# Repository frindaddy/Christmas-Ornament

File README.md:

# Christmas Ornament

A battery-powered, shake-activated LED ornament built around a Puya PY32F002B microcontroller. The KiCad files contain the schematic and PCB design; the firmware sleeps until the vibration switch detects movement, then alternates two LED groups.

## How It Works

- A CR2032 coin cell powers the board.
- An HX-0805-C2 vibration switch signals movement to PB0.
- The MCU wakes from STOP mode on either edge of the switch signal.
- Two LED groups, driven through N-channel MOSFETs from PB1 and PA7, alternate every 250 ms for about 5 seconds.
- The MCU returns to STOP mode after the pattern finishes.

The firmware targets the PY32F002BL15S7TU in an SOP-8 package. Battery life depends on the assembled circuit, components, and usage; no measured runtime is specified here.

## Repository Layout

| Path | Contents |
| --- | --- |
| [`hardware/Ornament.kicad_sch`](hardware/Ornament.kicad_sch) | KiCad schematic |
| [`hardware/Ornament.kicad_pcb`](hardware/Ornament.kicad_pcb) | KiCad PCB layout |
| [`hardware/Ornament.pretty/`](hardware/Ornament.pretty/) | Project-specific KiCad footprints |
| [`datasheets/`](datasheets/) | PY32F002B datasheet and reference manual |
| [`software/main.c`](software/main.c) | Application firmware |
| [`software/ornament.uvprojx`](software/ornament.uvprojx) | Keil µVision project |
| [`software/PY32F0xx_Drivers/`](software/PY32F0xx_Drivers/) | Used Puya low-level GPIO and EXTI driver sources |

## Firmware Pin Map

| MCU pin | Function |
| --- | --- |
| PB0 | Vibration switch input; external pull resistor is provided by the board |
| PB1 | LED group A MOSFET gate |
| PA7 | LED group B MOSFET gate |
| PA2 | SWCLK programming/debug signal |
| PB6 | SWDIO programming/debug signal |

## Build and Flash

The firmware project is configured for Keil µVision, Arm Compiler 6.24, and the Puya `PY32F0xx_DFP` device pack (version 1.2.8 in the project settings).

1. Install Keil MDK/µVision and the Puya PY32F0xx device family pack.
2. Open [`software/ornament.uvprojx`](software/ornament.uvprojx) in µVision and select the `Target_1` target.
3. Build the project. The configured executable output is `software/Objects/ornament.axf`.
4. Connect a SWD programmer to SWCLK (PA2), SWDIO (PB6), and the board's power/ground, then use µVision's download/debug controls to program the MCU.

## Hardware

Open the schematic and PCB in KiCad. The project includes custom footprints under `hardware/Ornament.pretty/` and local symbol/footprint table configuration files in `hardware/`. Confirm the selected fabrication settings and the PCB revision before ordering boards.

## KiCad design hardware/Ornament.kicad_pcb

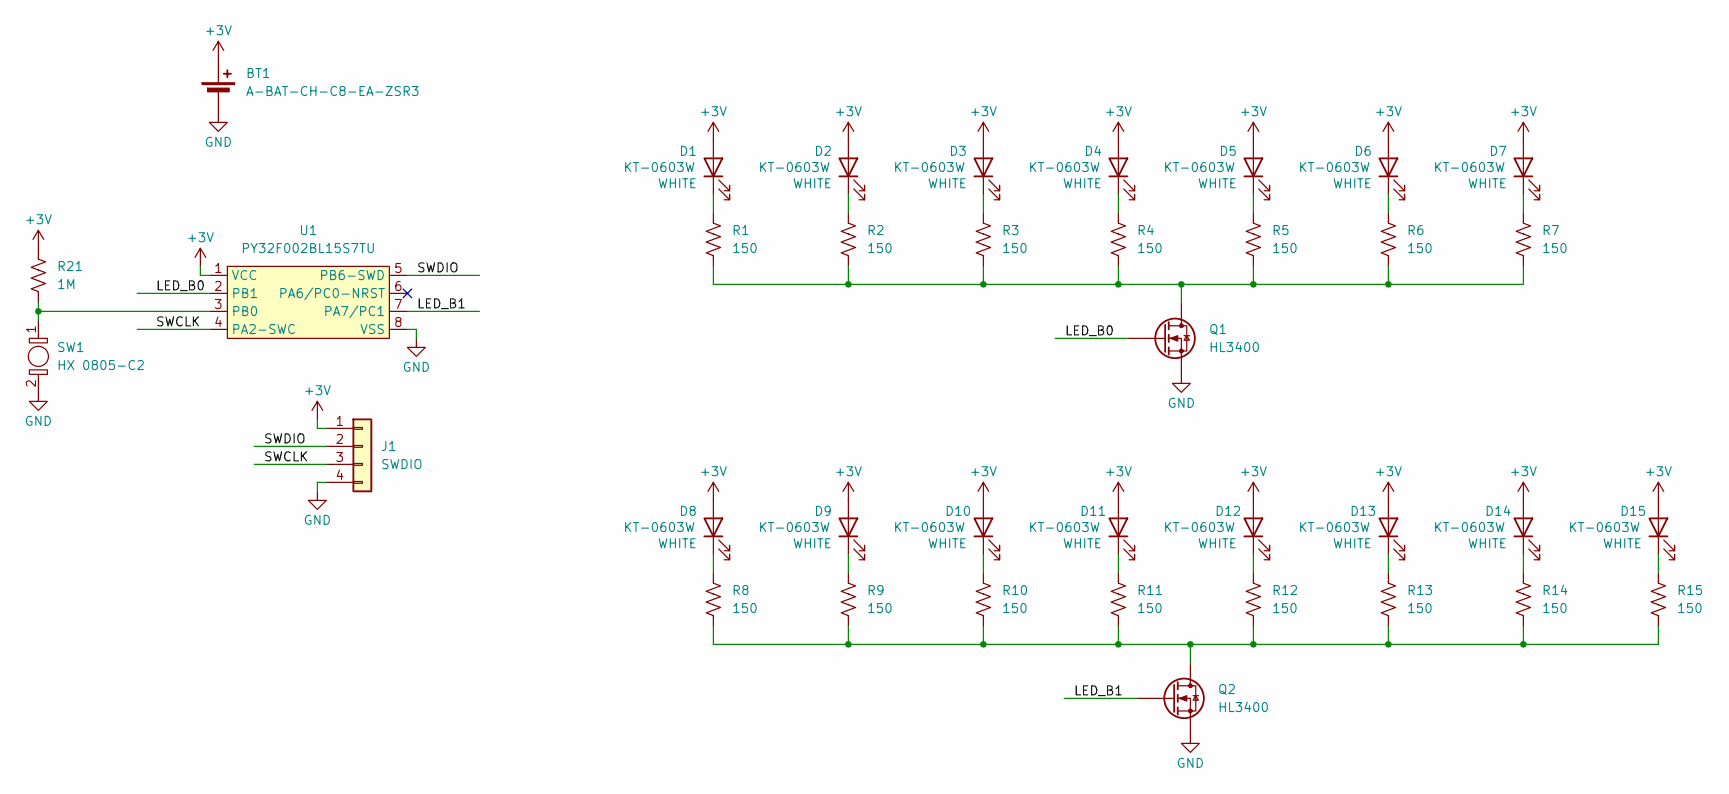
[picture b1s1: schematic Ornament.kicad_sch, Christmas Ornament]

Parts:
BT1: A-BAT-CH-C8-EA-ZSR3; CR2032-BS-6-1
D1, D2, D3, D4, D5, D6, D7, D8, D9, D10, D11, D12, D13, D14, D15: KT-0603W; LED_0603_1608Metric_Pad1.05x0.95mm_HandSolder; JLCPCB Part Number KT-0603W
J1: SWDIO; SWD_SMT_Pads
Q1, Q2: HL3400; SOT-23; JLCPCB Part Number C22469448
R1, R2, R3, R4, R5, R6, R7, R8, R9, R10, R11, R12, R13, R14, R15: 150; R_0603_1608Metric_Pad0.98x0.95mm_HandSolder; JLCPCB Part Number C22808
R21: 1M; R_0603_1608Metric_Pad0.98x0.95mm_HandSolder; JLCPCB Part Number C22935
SW1: HX 0805-C2; R_0805_2012Metric; JLCPCB Part Number C42371121
U1: PY32F002BL15S7TU; SOP-8_3.76x4.96mm_P1.27mm; JLCPCB Part Number C49424671

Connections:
+3V: BT1.1 (+), D1.2 (A), D2.2 (A), D3.2 (A), D4.2 (A), D5.2 (A), D6.2 (A), D7.2 (A), D8.2 (A), D9.2 (A), D10.2 (A), D11.2 (A), D12.2 (A), D13.2 (A), D14.2 (A), D15.2 (A), J1.1, R21.1, U1.1 (VCC)
/LED_B0: Q1.1 (G), U1.2 (PB1)
/LED_B1: Q2.1 (G), U1.7 (PA7/PC1)
/SWCLK: J1.3, U1.4 (PA2-SWC)
/SWDIO: J1.2, U1.5 (PB6-SWD)
GND: BT1.2 (-), J1.4, Q1.2 (S), Q2.2 (S), SW1.2, U1.8 (VSS)
unnamed: D1.1 (K), R1.1
unnamed: D2.1 (K), R2.1
unnamed: D3.1 (K), R3.1
unnamed: D4.1 (K), R4.1
unnamed: D5.1 (K), R5.1
unnamed: D6.1 (K), R6.1
unnamed: D7.1 (K), R7.1
unnamed: D8.1 (K), R8.1
unnamed: D9.1 (K), R9.1
unnamed: D10.1 (K), R10.1
unnamed: D11.1 (K), R11.1
unnamed: D12.1 (K), R12.1
unnamed: D13.1 (K), R13.1
unnamed: D14.1 (K), R14.1
unnamed: D15.1 (K), R15.1
unnamed: Q1.3 (D), R1.2, R2.2, R3.2, R4.2, R5.2, R6.2, R7.2
unnamed: Q2.3 (D), R8.2, R9.2, R10.2, R11.2, R12.2, R13.2, R14.2, R15.2
unnamed: R21.2, SW1.1, U1.3 (PB0)

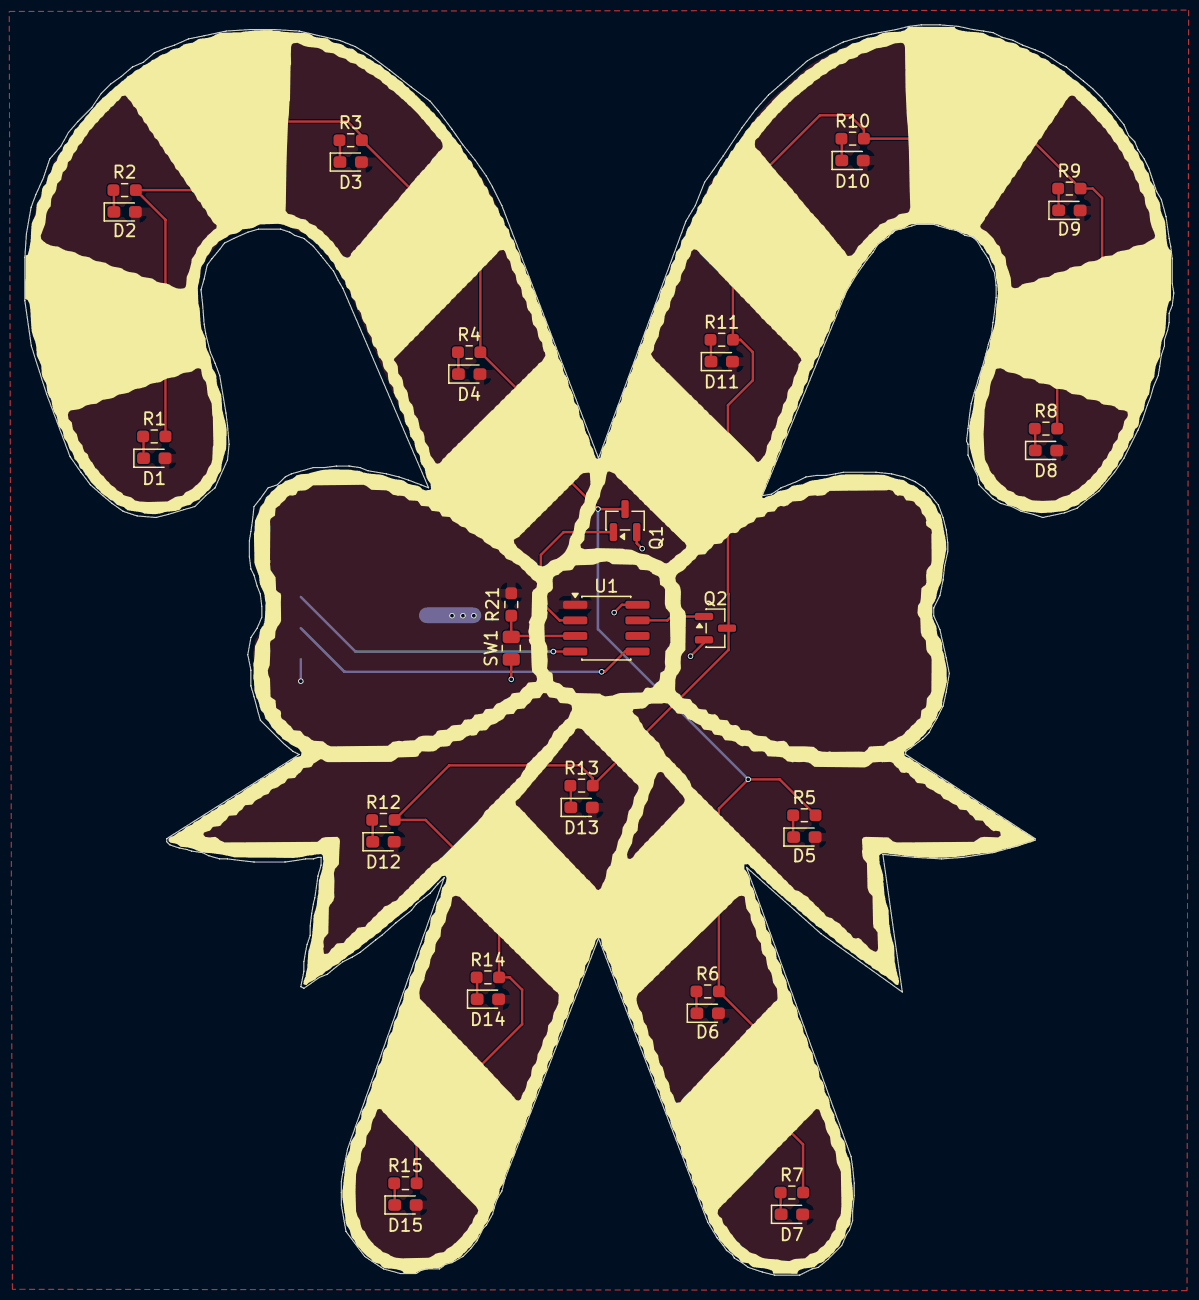
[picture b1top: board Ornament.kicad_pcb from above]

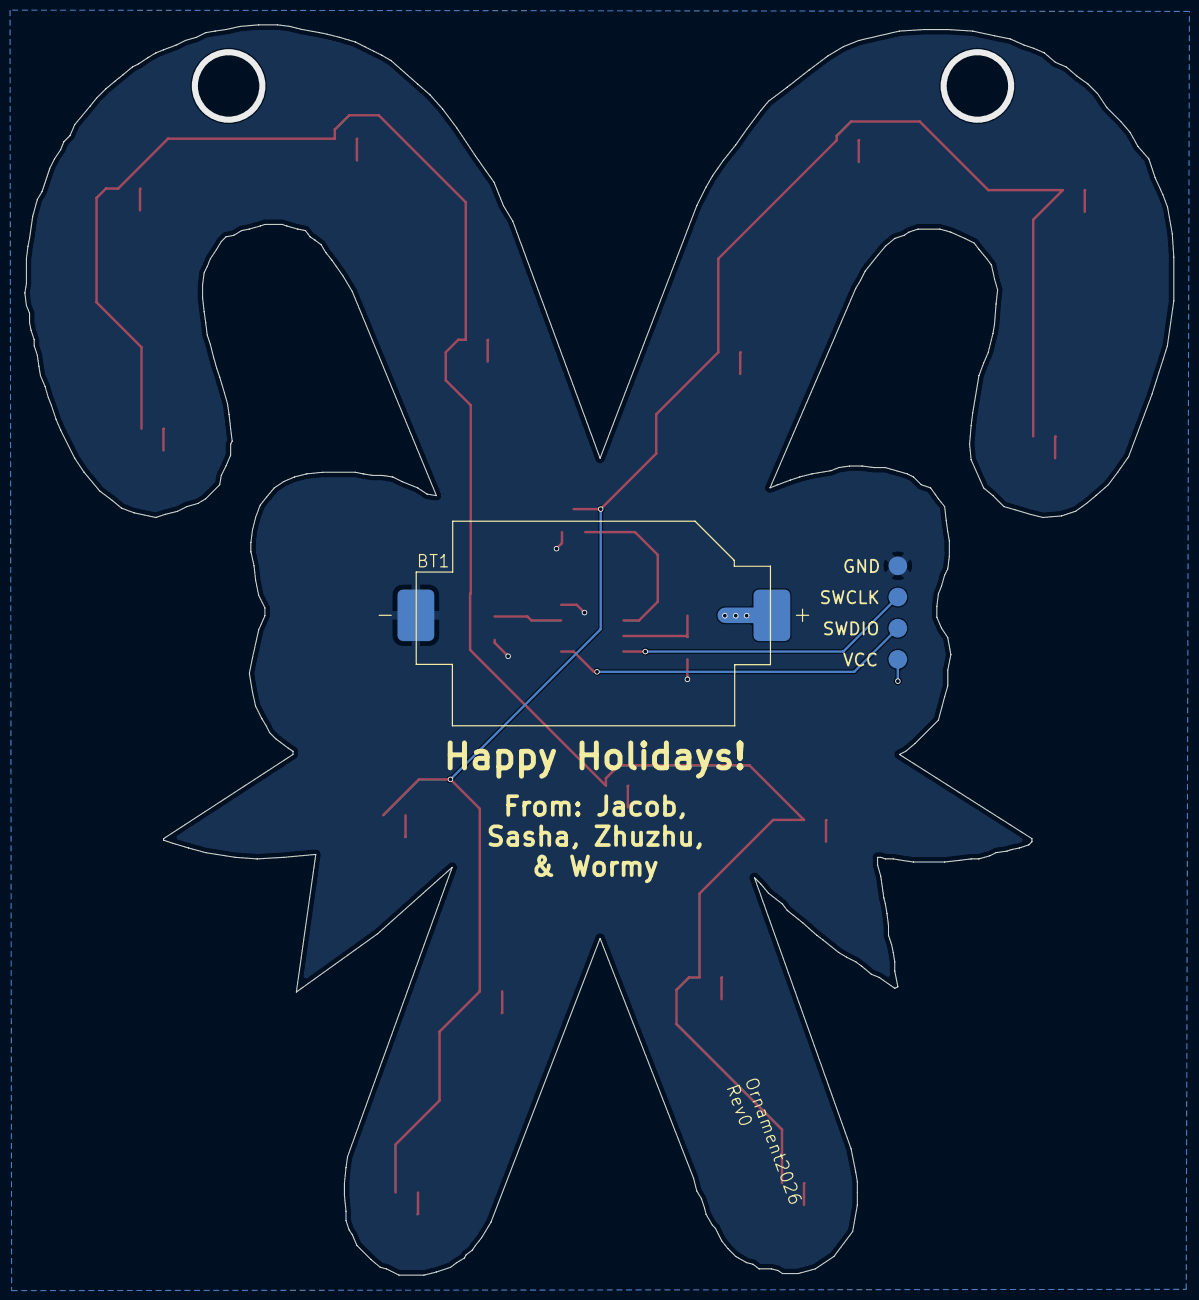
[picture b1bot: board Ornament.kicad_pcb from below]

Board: 2 copper layers, 93.6 x 101.9 mm, 37 parts (2 on the bottom side), 24 nets.

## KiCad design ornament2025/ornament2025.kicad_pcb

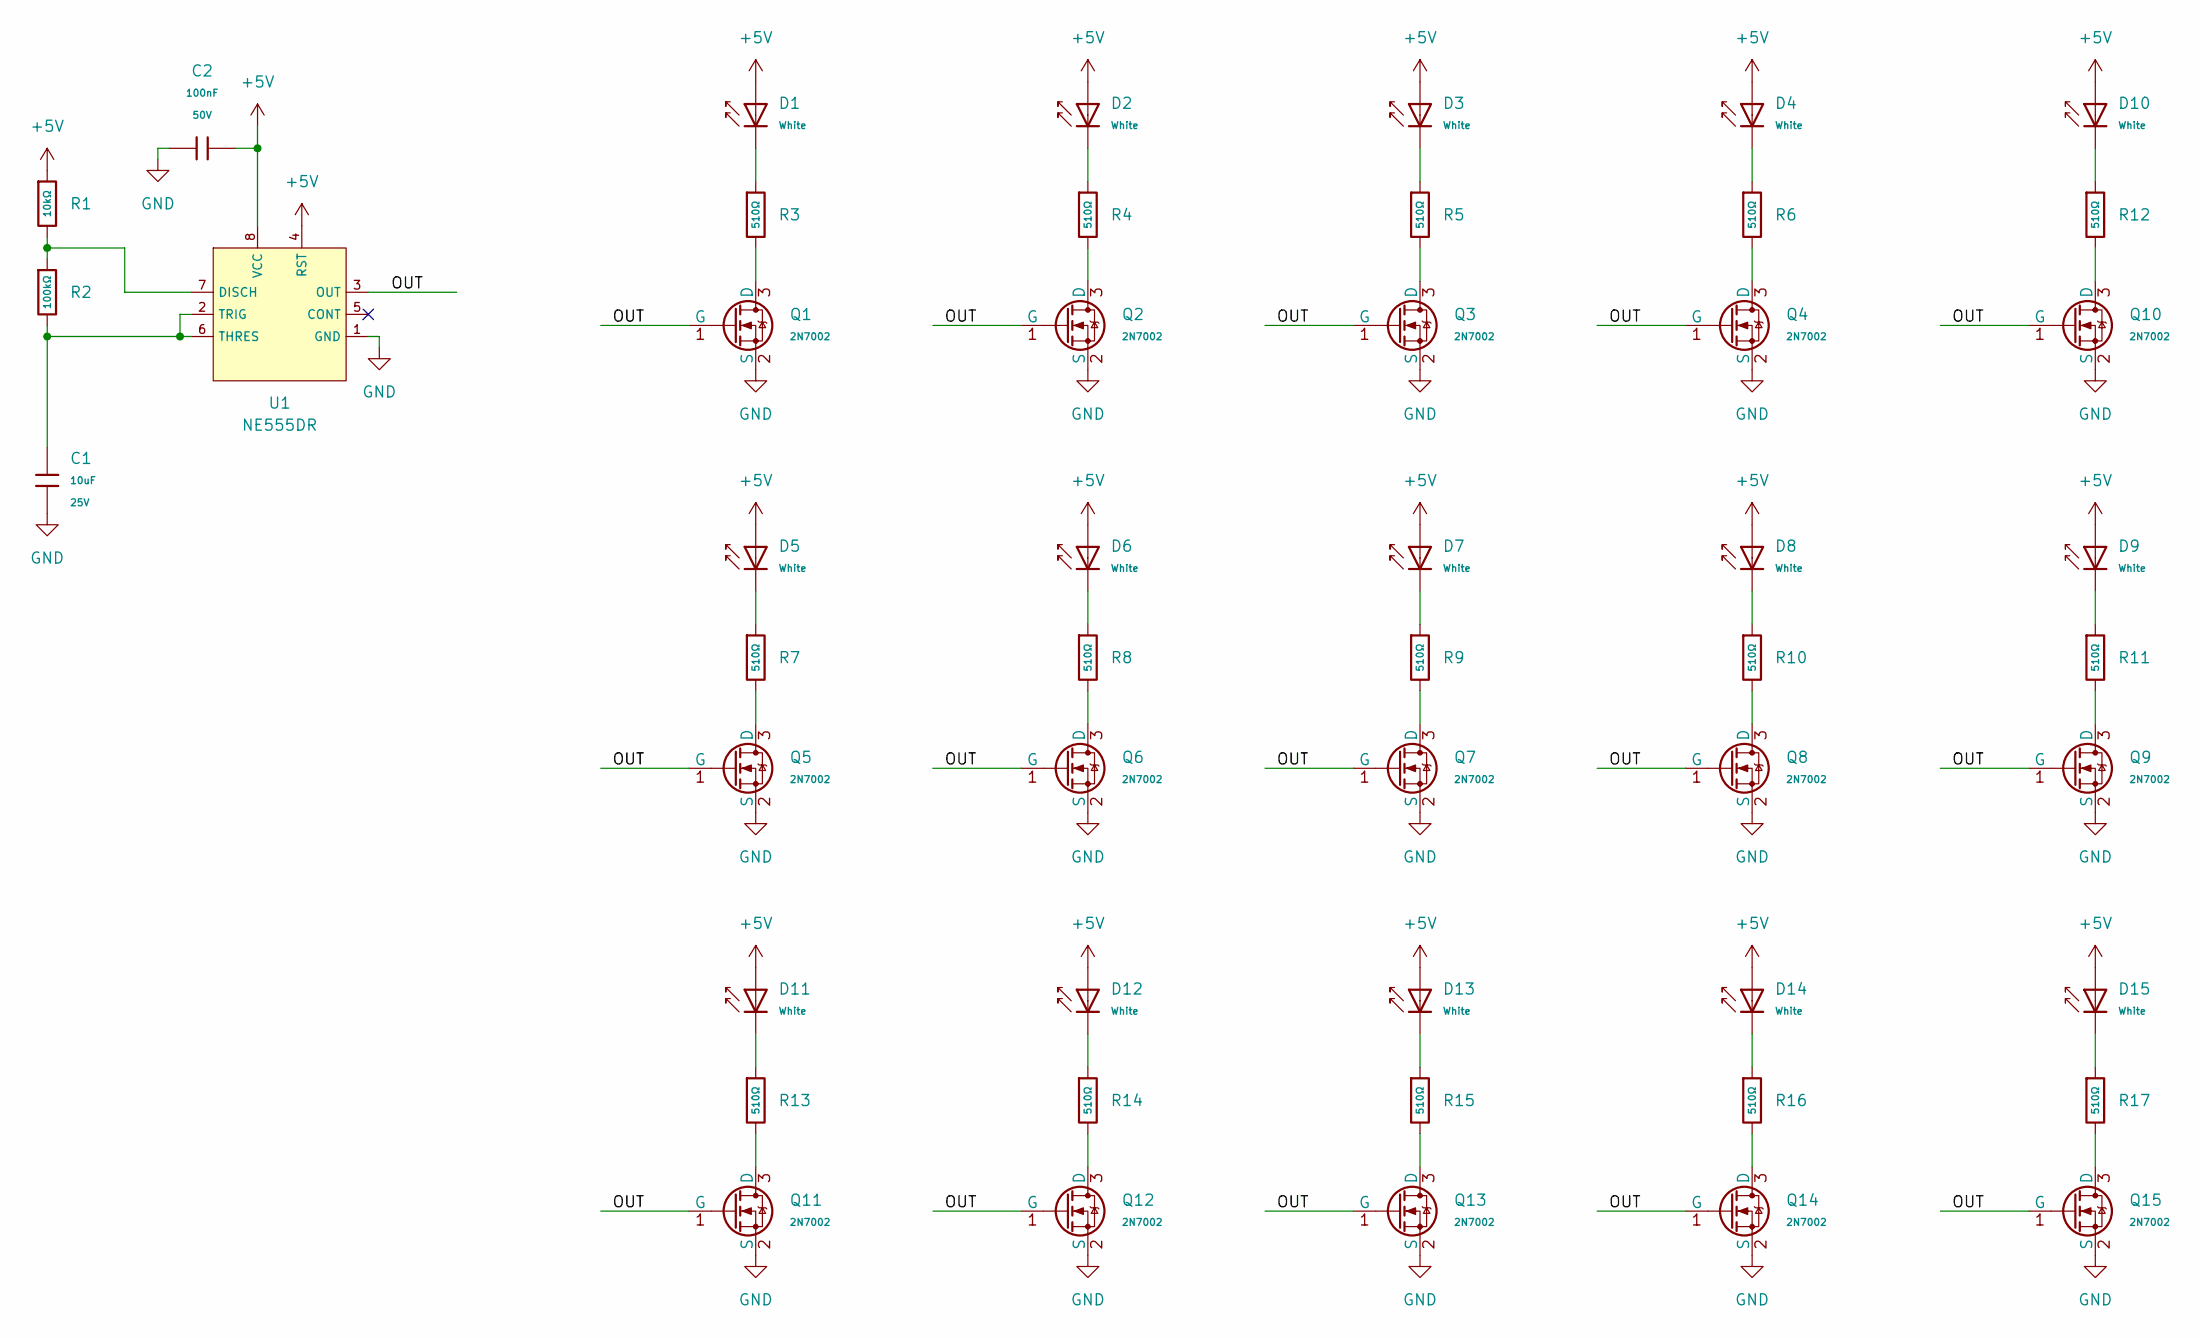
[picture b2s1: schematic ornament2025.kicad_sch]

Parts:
C1: 10uF; C_0805; Voltage Rated 25V; Tolerance ±10%; Part CL21A106KAYNNNE; LCSC C15850
C2: 100nF; C_0603; Voltage Rated 50V; Tolerance ±10%; Part CC0603KRX7R9BB104; LCSC C14663
D1, D2, D3, D4, D5, D6, D7, D8, D9, D10, D11, D12, D13, D14, D15: White; D_0805; Part KT-0805W; LCSC C34499
Q1, Q2, Q3, Q4, Q5, Q6, Q7, Q8, Q9, Q10, Q11, Q12, Q13, Q14, Q15: 2N7002; Q_SOT-23; Part 2N7002; LCSC C8545
R1: 10kΩ; R_0402; Overload Voltage (Max) 50V; Tolerance ±1%; Part 0402WGF1002TCE; LCSC C25744
R2: 100kΩ; R_0402; Overload Voltage (Max) 50V; Tolerance ±1%; Part 0402WGF1003TCE; LCSC C25741
R3, R4, R5, R6, R7, R8, R9, R10, R11, R12, R13, R14, R15, R16, R17: 510Ω; R_0402; Overload Voltage (Max) 50V; Tolerance ±1%; Part 0402WGF5100TCE; LCSC C25123
U1: NE555DR; SOIC-8_L4.9-W3.9-P1.27-LS6.0-BL; Supply Voltage 4.5V~16V; Part NE555DR; LCSC C7593

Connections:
+5V: C2.2, D1.2, D2.2, D3.2, D4.2, D5.2, D6.2, D7.2, D8.2, D9.2, D10.2, D11.2, D12.2, D13.2, D14.2, D15.2, R1.1, U1.4 (RST), U1.8 (VCC)
/OUT: Q1.1 (G), Q2.1 (G), Q3.1 (G), Q4.1 (G), Q5.1 (G), Q6.1 (G), Q7.1 (G), Q8.1 (G), Q9.1 (G), Q10.1 (G), Q11.1 (G), Q12.1 (G), Q13.1 (G), Q14.1 (G), Q15.1 (G), U1.3 (OUT)
GND: C1.2, C2.1, Q1.2 (S), Q2.2 (S), Q3.2 (S), Q4.2 (S), Q5.2 (S), Q6.2 (S), Q7.2 (S), Q8.2 (S), Q9.2 (S), Q10.2 (S), Q11.2 (S), Q12.2 (S), Q13.2 (S), Q14.2 (S), Q15.2 (S), U1.1 (GND)
unnamed: D1.1, R3.1
unnamed: D2.1, R4.1
unnamed: D3.1, R5.1
unnamed: D4.1, R6.1
unnamed: D5.1, R7.1
unnamed: D6.1, R8.1
unnamed: D7.1, R9.1
unnamed: D8.1, R10.1
unnamed: D9.1, R11.1
unnamed: D10.1, R12.1
unnamed: D11.1, R13.1
unnamed: D12.1, R14.1
unnamed: D13.1, R15.1
unnamed: D14.1, R16.1
unnamed: D15.1, R17.1
unnamed: Q1.3 (D), R3.2
unnamed: Q2.3 (D), R4.2
unnamed: Q3.3 (D), R5.2
unnamed: Q4.3 (D), R6.2
unnamed: Q5.3 (D), R7.2
unnamed: Q6.3 (D), R8.2
unnamed: Q7.3 (D), R9.2
unnamed: Q8.3 (D), R10.2
unnamed: Q9.3 (D), R11.2
unnamed: Q10.3 (D), R12.2
unnamed: Q11.3 (D), R13.2
unnamed: Q12.3 (D), R14.2
unnamed: Q13.3 (D), R15.2
unnamed: Q14.3 (D), R16.2
unnamed: Q15.3 (D), R17.2
unnamed: R1.2, R2.1, U1.7 (DISCH)
unnamed: C1.1, R2.2, U1.2 (TRIG), U1.6 (THRES)

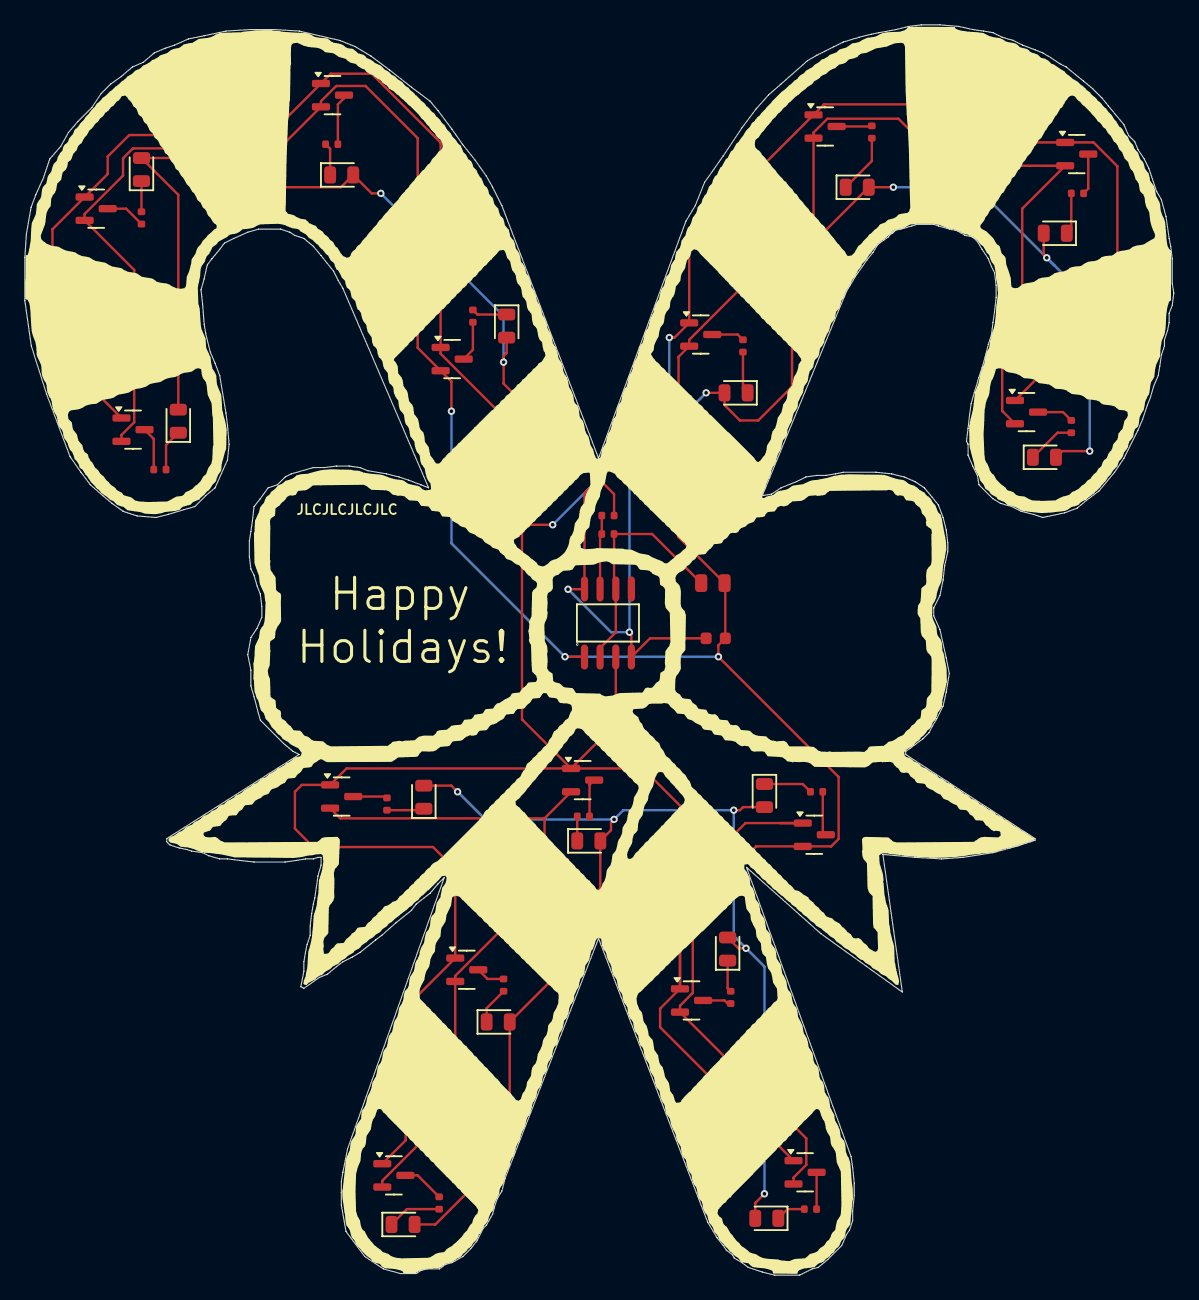
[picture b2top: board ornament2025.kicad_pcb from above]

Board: 2 copper layers, 93.6 x 101.9 mm, 51 parts (0 on the bottom side), 35 nets.

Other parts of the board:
PN1: Part_Num_JLCPCB

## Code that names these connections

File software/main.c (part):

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 * ----------------------------------------------------------------------------
 * The board sits in low-power STOP mode almost all the time, drawing close
 * to nothing from the battery. A mechanical vibration switch (HX-0805-C2) on
 * pin PB0 chatters between high and low whenever the ornament is bumped or
 * shaken. That level change wakes the chip via an EXTI (external interrupt)
 * on line 0.
 *
 * Once awake, the firmware alternates two groups of LEDs -- Group A on PB1,
 * Group B on PA7, each driven through its own N-MOSFET -- switching which
 * group is lit roughly every 250ms, for about 5 seconds total. After that,
 * both groups turn off and the chip drops straight back into STOP mode to
 * wait for the next shake.
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 *
 * PIN MAP
 * ----------------------------------------------------------------------------
 *   PB0  - vibration switch input (external 1-10M pull resistor on the PCB
 *          does the pulling; this pin is configured as a plain floating
 *          input, not using the MCU's internal pull)
 *   PB1  - gate of the N-MOSFET driving LED group A
 *   PA7  - gate of the N-MOSFET driving LED group B
 *   PA2  - SWCLK (left alone here; used only for programming/debug)
 *   PB6  - SWDIO (left alone here; used only for programming/debug)
 *
 * TIMING
 * ----------------------------------------------------------------------------
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#include "py32f0xx_ll_exti.h"

/* ---- Pin assignments -------------------------------------------------- */
#define LED_GROUP_A_PIN   LL_GPIO_PIN_1   /* PB1 */
#define LED_GROUP_B_PIN   LL_GPIO_PIN_7   /* PA7 */
#define SWITCH_PIN        LL_GPIO_PIN_0   /* PB0 */

/* ---- Pattern timing ----------------------------------------------------
 * PATTERN_DURATION_MS: how long the LED show runs after being woken.
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/* -----------------------------------------------------------------------
 * GPIO_Config
 *   Sets up every pin this design touches:
 *     - PB1, PA7 as push-pull outputs, both driven low (LEDs off) at boot
 *     - PB0 as a floating input (external resistor network on the board
 *       does the pull-up, so no internal pull is enabled here)
 * ------------------------------------------------------------------------- */
static void GPIO_Config(void)
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
/* -----------------------------------------------------------------------
 * EXTI_Config
 *   Routes PB0 to EXTI line 0 and arms it to interrupt on either a rising
 *   or falling edge, since a real shake produces a chattery burst of both
 *   directions rather than one clean transition.
 * ------------------------------------------------------------------------- */
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    exti_init.Trigger = LL_EXTI_TRIGGER_RISING_FALLING;
    LL_EXTI_Init(&exti_init);

    /* Map EXTI line 0 to GPIO port B, so it watches PB0 specifically
       rather than PA0 or PC0 (all three share line 0 on this family). */
    LL_EXTI_SetEXTISource(LL_EXTI_CONFIG_PORTB, LL_EXTI_CONFIG_LINE0);

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
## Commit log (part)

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2025-11-25 sch and layout. no battery
